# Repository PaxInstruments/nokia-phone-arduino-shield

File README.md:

# Pax Instruments
# Nokia Phone Arduino Shield

## Overview
This project is the Pax Instruments Nokia Phone Arduino Shield

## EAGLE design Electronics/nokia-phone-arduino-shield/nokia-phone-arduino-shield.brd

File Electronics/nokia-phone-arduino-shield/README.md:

# Pax Instruments
# lcd12364-shield

Developed by <person(s) name> for [Pax Instruments](http://paxinstruments.com/), an original design.

## Overview
This is the electronics for the Pax Instruments JT-100 Junction Thermometer designed in Cadsoft Eagle.

## License
```
Place the license statement here
```

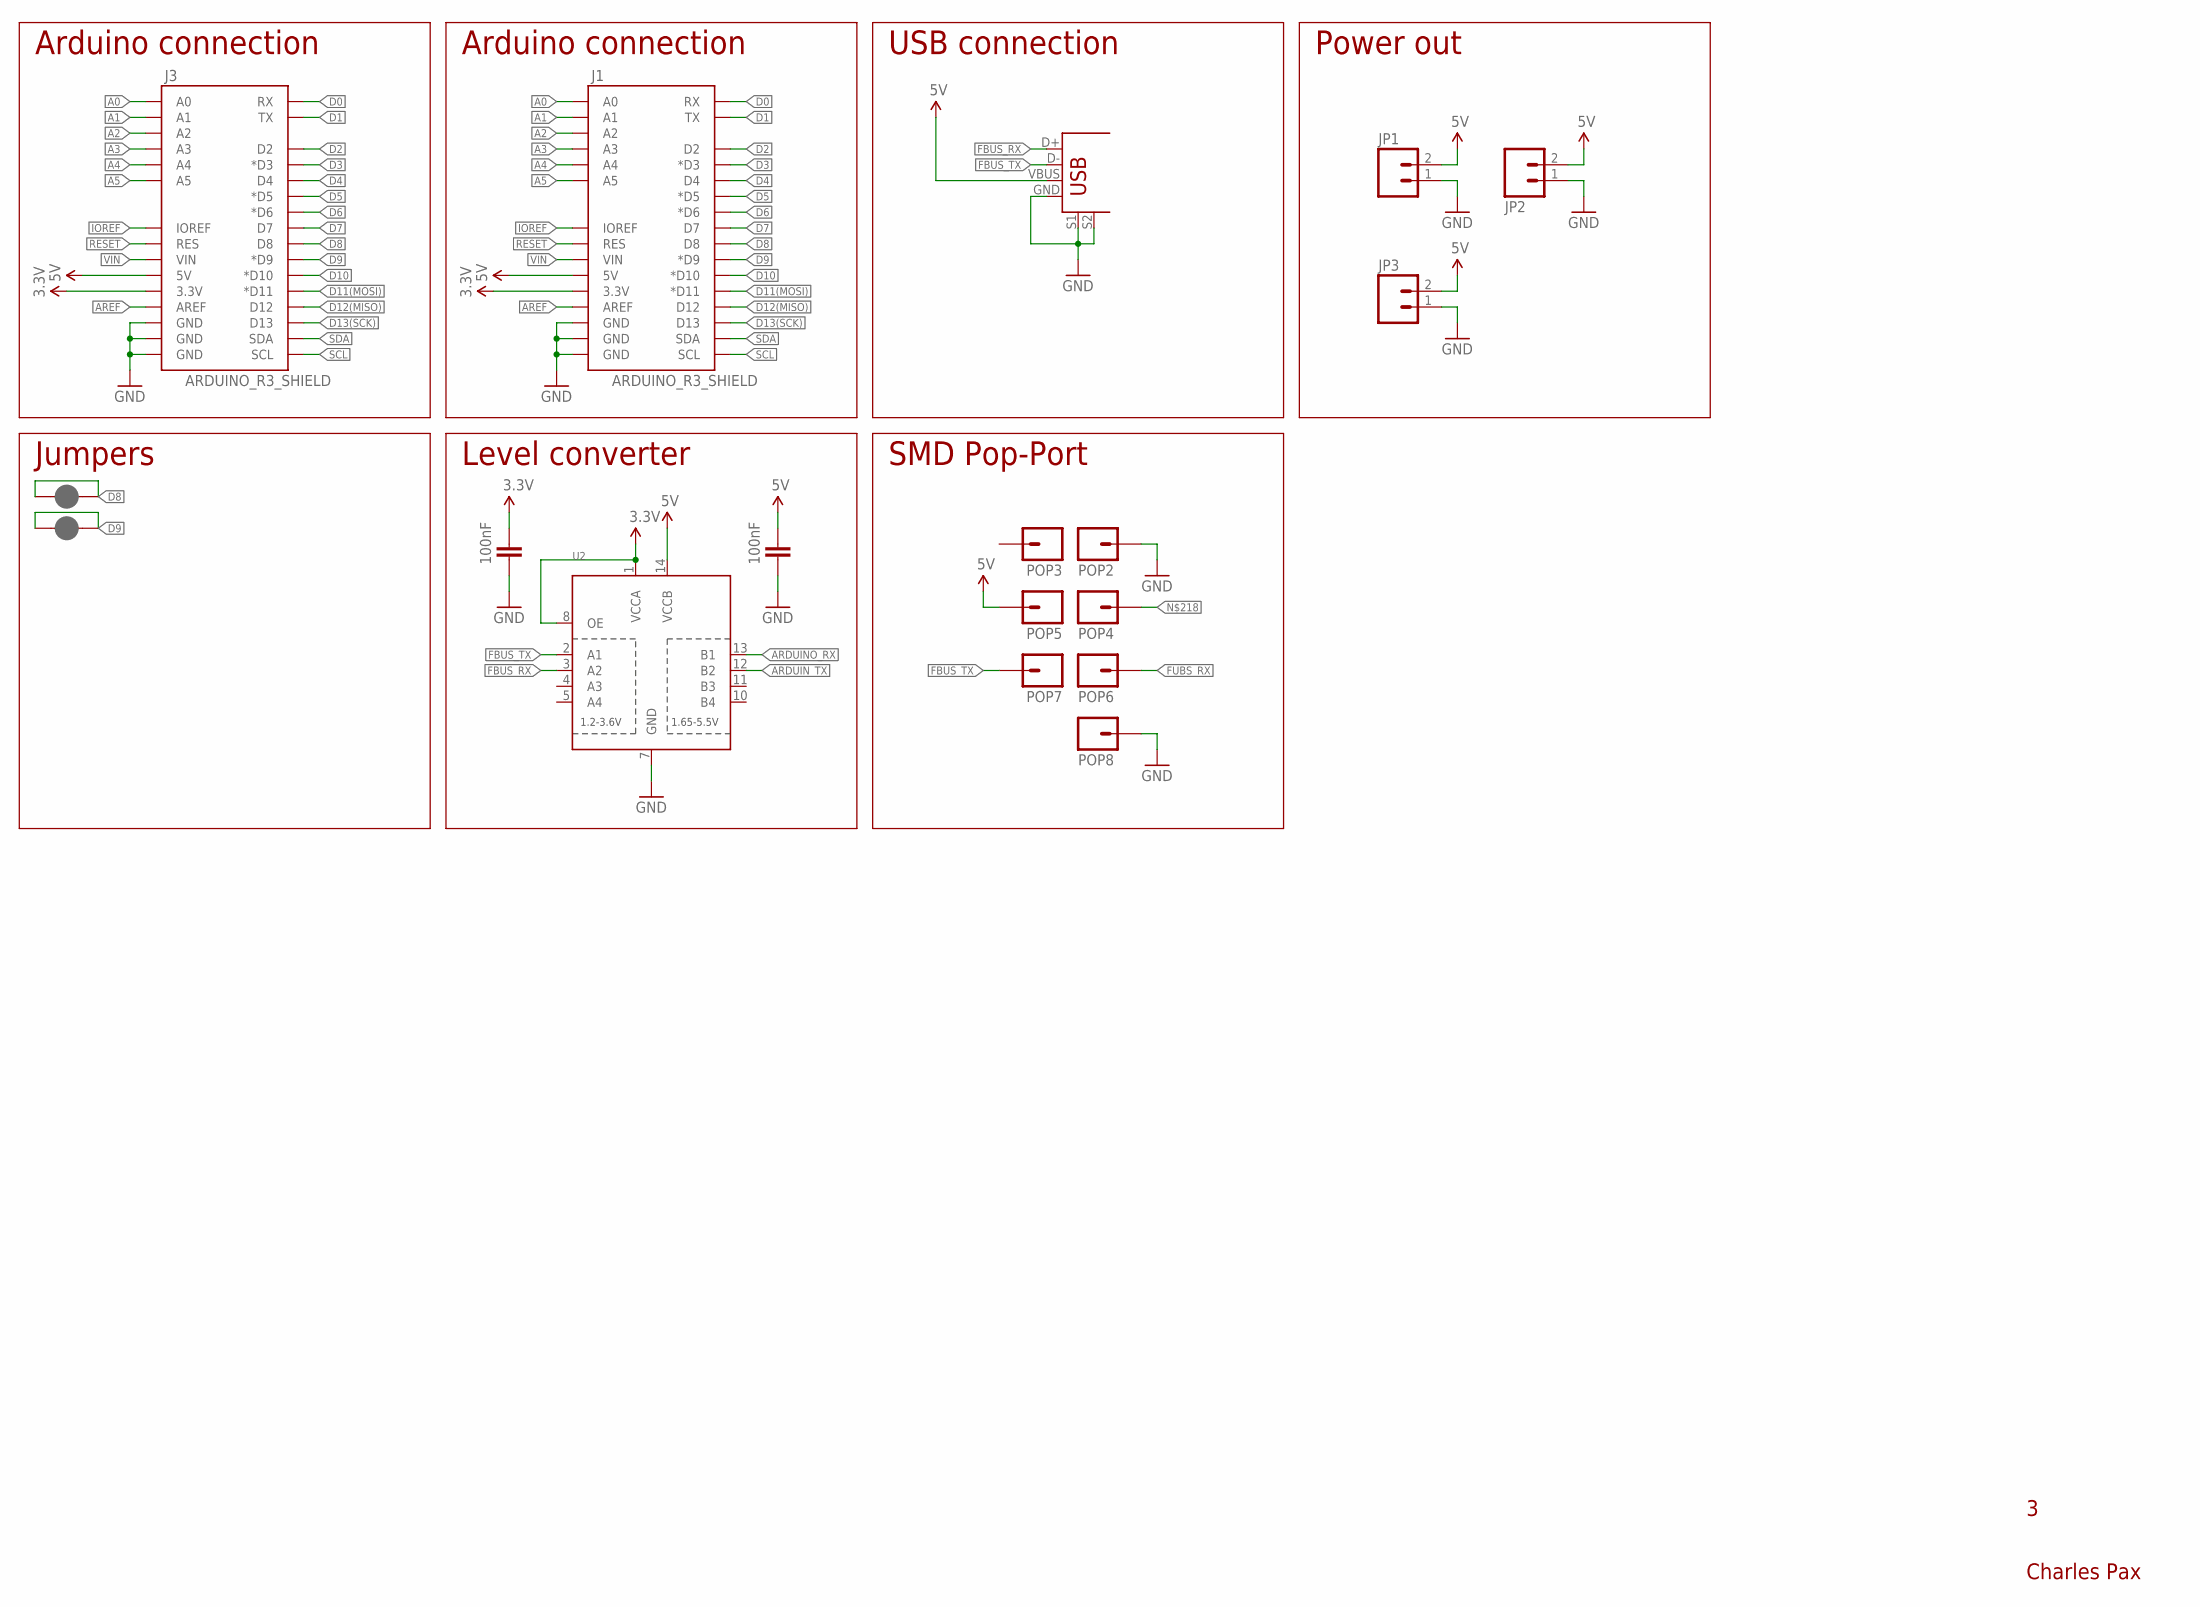
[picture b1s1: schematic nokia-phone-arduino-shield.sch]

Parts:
C3, C4: 100nF; SPARKFUN-CAPACITORS_0603-CAP; MPN CL10B104KO8NNNC
J1, J3: ARDUINO_R3_SHIELD; UNO_R3_SHIELD_NOLABELS_LOCK
JP1, JP3: M02LOCK; 1X02_LOCK
JP2: M02-JST-2MM-SMT; JST-2-SMD
POP2, POP3, POP4, POP5, POP6, POP7, POP8: M01SMD-4.5X1.5; PAD-1.5X4.5
SJ21, SJ22: JUMPER-PAD-2-NC_BY_PASTE; PAD-JUMPER-2-NC_BY_PASTE_YES_SILK
U2: TXB0104PWRSOIC14; SO14; MPN TXB0104DR
U$2: USB+SHIELDUSB-A-S-NOSILK-FEMALE; USB-A-S-NOSILK-FEMALE

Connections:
3.3V: C3.2, J1.3.3V, J3.3.3V, U2.1 (VCCA), U2.8 (OE)
5V: C4.2, J1.5V, J3.5V, JP1.2, JP2.2 (1), JP3.2, POP5.P$1, U2.14 (VCCB), U$2.VBUS
A0: J1.A0, J3.A0
A1: J1.A1, J3.A1
A2: J1.A2, J3.A2
A3: J1.A3, J3.A3
A4: J1.A4, J3.A4
A5: J1.A5, J3.A5
ARDUINO_RX: U2.13 (B1)
ARDUIN_TX: U2.12 (B2)
AREF: J1.AREF, J3.AREF
D0: J1.RX, J3.RX
D1: J1.TX, J3.TX
D2: J1.D2, J3.D2
D3: J1.D3 (*D3), J3.D3 (*D3)
D4: J1.D4, J3.D4
D5: J1.D5 (*D5), J3.D5 (*D5)
D6: J1.D6 (*D6), J3.D6 (*D6)
D7: J1.D7, J3.D7
D8: J1.D8, J3.D8, SJ21.1, SJ21.2
D9: J1.D9 (*D9), J3.D9 (*D9), SJ22.1, SJ22.2
D10: J1.D10 (*D10), J3.D10 (*D10)
D11(MOSI): J1.D11 (*D11), J3.D11 (*D11)
D12(MISO): J1.D12, J3.D12
D13(SCK): J1.D13, J3.D13
FBUS_RX: U2.3 (A2), U$2.D+
FBUS_TX: POP7.P$1, U2.2 (A1), U$2.D-
FUBS_RX: POP6.P$1
GND: C3.1, C4.1, J1.GND@0 (GND), J1.GND@1 (GND), J1.GND@2 (GND), J3.GND@0 (GND), J3.GND@1 (GND), J3.GND@2 (GND), JP1.1, JP2.1 (2), JP3.1, POP2.P$1, POP8.P$1, U2.7 (GND), U$2.GND, U$2.S1, U$2.S2
IOREF: J1.IOREF, J3.IOREF
RESET: J1.RES, J3.RES
SCL: J1.SCL, J3.SCL
SDA: J1.SDA, J3.SDA
VIN: J1.VIN, J3.VIN

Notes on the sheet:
Charles Pax
Arduino connection
Jumpers
Level converter
USB connection
SMD Pop-Port
Power out

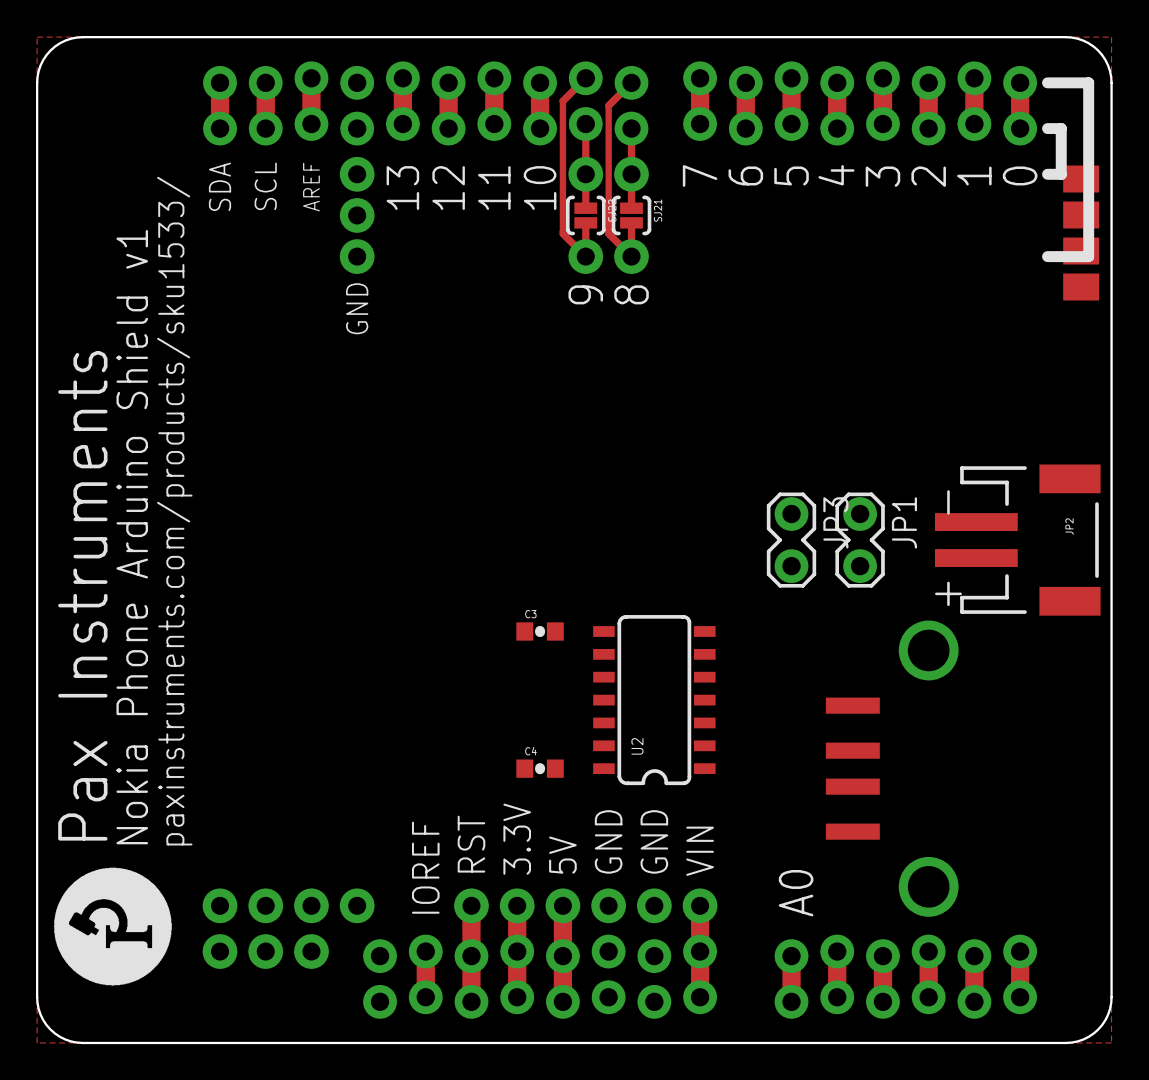
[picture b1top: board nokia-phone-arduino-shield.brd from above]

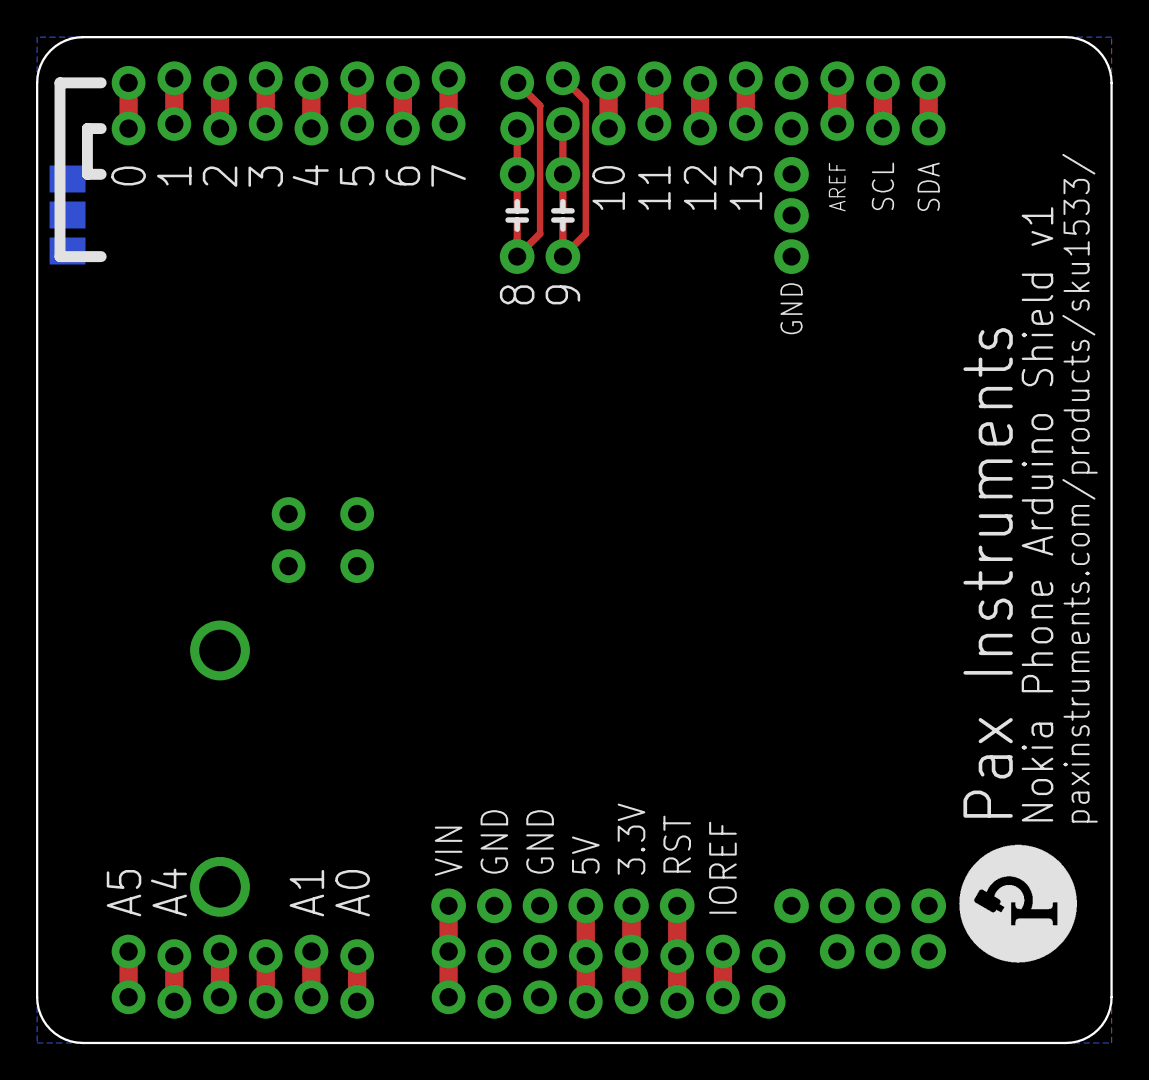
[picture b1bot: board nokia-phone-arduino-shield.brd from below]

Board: 2 copper layers, 59.7 x 55.9 mm, 20 parts (4 on the bottom side), 31 nets.

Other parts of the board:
U$1, U$6: PAXINSTRUMENT_LOGO

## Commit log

2015-05-19 Added nearly blank Arduino sketch.
2015-05-20 We can get phone info.
2015-05-20 Program can display hardware and software information to the serial port. Does not process packet, just displays a range of bytes in the array.
2015-05-20 Added a testFun() function for testing messages.
2015-05-20 We can now receive the HW/SW infor without debug mode. We just needed to add a delay.
2015-05-20 Works using AltSoftSerial.h to connect to the phone on pin 8 and 9 on the Arduino Uno.
2015-05-20 Small fix.
2015-05-22 Moved prepare() command into the send() function. It should be called individually from each function.
2015-05-22 Removed redundant function, moved to Serial.write(message,sizeof(message)) instead.
2015-05-22 Removed testFun().
2015-05-23 All functions moved to FBus library. At parity.
2015-05-23 SW version, HW version, and date code are in functions. Each returns a String of the appropriate value. However, there is some strange characters at the end and a new line character at the beginning.
2015-05-23 Fixed a leading linebreak issue. Still have strange trailing characters.
2015-05-24 Code cleanup.
2015-05-25 Added a basic shield with connections. Need to route.
2015-05-25 Routed and ready.
2015-05-25 Added v1 files. Ordering now.
2015-05-25 Added gnokii documentation for the Nokia 3100 phone and F-Bus protocol. Added template functions for Arduino sketch. Added F-Bus research notes.
2015-05-25 Added some more notes.
2015-05-28 This shoudl work. Not sure what's wrong. Hardware problem. Added notes.
2015-05-28 Using SoftwareSerial.h and not AltSoftwareSerial.h, which seems to have some interrupt stuff that breaks up the initialize() command.
2015-05-28 Removed/modified the delays
2015-05-28 Disabled getting additional sw/hw info until messages get parsed correctly.
2015-06-05 Able to read a packet from beginning to end.
2015-06-05 Can checksum the packet.
2015-06-05 Automatically sends the correct acknowledgement packet.
2015-06-06 Can create a HWSW request packet in a basic way. Can checksum the packet being created.
2015-06-06 Modified for Arduino Leonardo. Added debug info.
2015-06-06 Added a bunch of comments.
2015-06-06 Removed all the old code.
2015-06-07 Added aswitch statement to the notes. This should process individual bytes as they come in.
2015-06-07 Switch statement added to Arduion code. Code compiles, but it not implemented.
2015-06-08 Almost ready. see ntoes.
2015-06-09 Not qite working yet, but close.
2015-06-10 Still banging my head.
2015-06-11 The packet structure method can now do proper checksums and send the correct acknowledgement packet.
2015-06-11 Adding files to write the SMS packer code.
2015-06-11 Added requestHWSW(). Fixed a packetSend() bug.
2015-06-11 Added temaplte HW and SW functions.
2015-06-12 sendACK() uses the packet structure.
2015-06-12 Removed obsolete code.
2015-06-12 Library can return hardware, software, and date information.
2015-06-19 Added some functions that I'be been playing with.
2015-06-22 Updated variable names to no conflict with the user code, added some new types that match with frame structure on the wire. Added some new logic for sending packet.
    Stripped down the main code for testing
2015-06-23 Got TX packet working, checksum correct, endianness is correct and it uses fewer loops
2015-06-23 Added docs.
2015-06-23 Added bit packing algorithm and the start of an SMS send function. Added pinout diagram
2015-06-24 SMS packet matches the example from Embedtronics, except where they have a random F0 at the end of the SMSC number. Can add that in and it will be prefect
2015-06-24 Removed unsuded gnokii protocol file. Added several possible gnokii protocol files.
2015-06-25 Added SMSC numbers for china. Increased the number of 0x55 we send to start
2015-06-25 Renamed some variables and removed some old code
2015-06-25 Fixed ACKing packets, added some new 'states' to the RX packet so we know if we are NEW, RECEIVING, or READY for processing. Updated comments and organized everything so the header matches the body.
    Fixed up the ino file to be a good example of how this works
2016-08-26 Added randome files. Backing up.

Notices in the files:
parts and their libraries:
SparkFun-Boards: Licensing: Creative Commons ShareAlike 4.0 International - https://creativecommons.org/licenses/by-sa/4.0
SparkFun-Aesthetics: Licensing: CC v3.0 Share-Alike You are welcome to use this library for commercial purposes.
